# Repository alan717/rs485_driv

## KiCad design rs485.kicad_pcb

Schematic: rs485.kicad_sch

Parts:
J1, J3: Conn_01x12_Pin; PinHeader_1x12_P2.54mm_Vertical
U1: SOIC127P600X175-8N
U2: SN74CB3Q3384APW; TSSOP-24_4.4x7.8mm_P0.65mm

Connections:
GND: J1.9, U1.5 (GND), U2.12 (GND)
unnamed: J1.1, U2.23 (2B5)
unnamed: J1.2, U2.20 (2B4)
unnamed: J1.3, U2.19 (2B3)
unnamed: J1.4, U2.16 (2B2)
unnamed: J1.5, U2.15 (2B1)
unnamed: J1.6, U2.10 (1B5)
unnamed: J1.7, U2.9 (1B4)
unnamed: J1.8, U2.3 (1A1)
unnamed: J1.10, U1.6 (B)
unnamed: J1.11, U1.7 (A)
unnamed: J3.1, U2.2 (1B1)
unnamed: J3.2, U2.4 (1A2)
unnamed: J3.3, U2.7 (1A3)
unnamed: J3.4, U2.8 (1A4)
unnamed: J3.5, U2.11 (1A5)
unnamed: J3.6, U2.14 (2A1)
unnamed: J3.7, U2.17 (2A2)
unnamed: J3.8, U2.18 (2A3)
unnamed: J3.9, U2.21 (2A4)
unnamed: J3.10, U2.22 (2A5)
unnamed: J3.11, U2.1 (~1OE)
unnamed: J3.12, U2.13 (~2OE)
unnamed: U1.1 (R), U1.4 (D), U2.5 (1B2)
unnamed: U1.2 (RE~), U1.3 (DE), U2.6 (1B3)
VCC: J1.12, U1.8 (VCC), U2.24 (VCC)

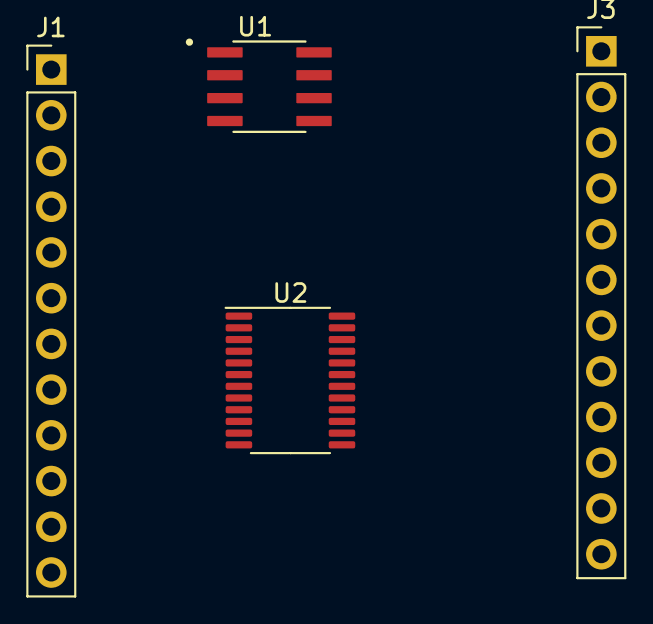
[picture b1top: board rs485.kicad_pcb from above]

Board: 2 copper layers, 4 parts (0 on the bottom side), 26 nets, no tracks yet.

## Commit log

2023-08-24 firts
2023-08-24 ADD.
2023-08-25 add readme./
2023-08-25 sch of.
2023-08-26 sch ok.
2023-08-28 update all.
2023-08-29 add footprint.lib
2023-08-29 up/.
2023-08-30 add pcb file.
2023-08-31 pcb ok.
2023-09-06 ADD .
2023-09-07 pcb开始制作了。
2023-09-11 之前的没问题，现在重新设计，重新制作一个，加电源稳压的电容。
2023-09-12 update 原理图，增加滤波。电容。暂时先不进行。
2023-10-29 remove backup.
